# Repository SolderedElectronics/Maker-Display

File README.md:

# Maker Display
## Image

[Crowdsupply campaign][CF]

## Description and details
Maker LED display brings simplicity when it comes to using LED Matrix Displays. Ready to use, assembled circuit board has everything you need to run the display - just plug it in! Arduino library written for it and a dozen pre-made examples make using and customization of the display a trivial task. Not to forget the WiFi connection which enables board to get various info and show it to you. There’s more than just customization of content shown on the display! Choose between 32 x 9 pixels or 64 x 9 pixels version and pick the LED color: white, blue, green, orange or purple.

## Repository content
This repo contains Cadsoft Eagle .sch and .brd files for the board. It also contains schematic in .pdf created from .sch Eagle file. 
Files have been arranged into folders for navigating between different versions of board. 
Tip: layer 200 shows top silkscreen and layer 208 should be bottom silkscreen. tParts and bParts are not used.

## Docs
- [Maker Display Campaign][CF]
- [Maker Display Arduino Library][library]

## Board versions
- v1.0 - inital version

## License info
This product is open-source. Yay!
For any tech questions, contact us at techsupport@e-radionica.com
If you find an Issue, please open one at GitHub. If you can improve our product, fork it!

e-r.io Team.

[library]: #
[CF]: https://www.crowdsupply.com/e-radionica/maker-led-display

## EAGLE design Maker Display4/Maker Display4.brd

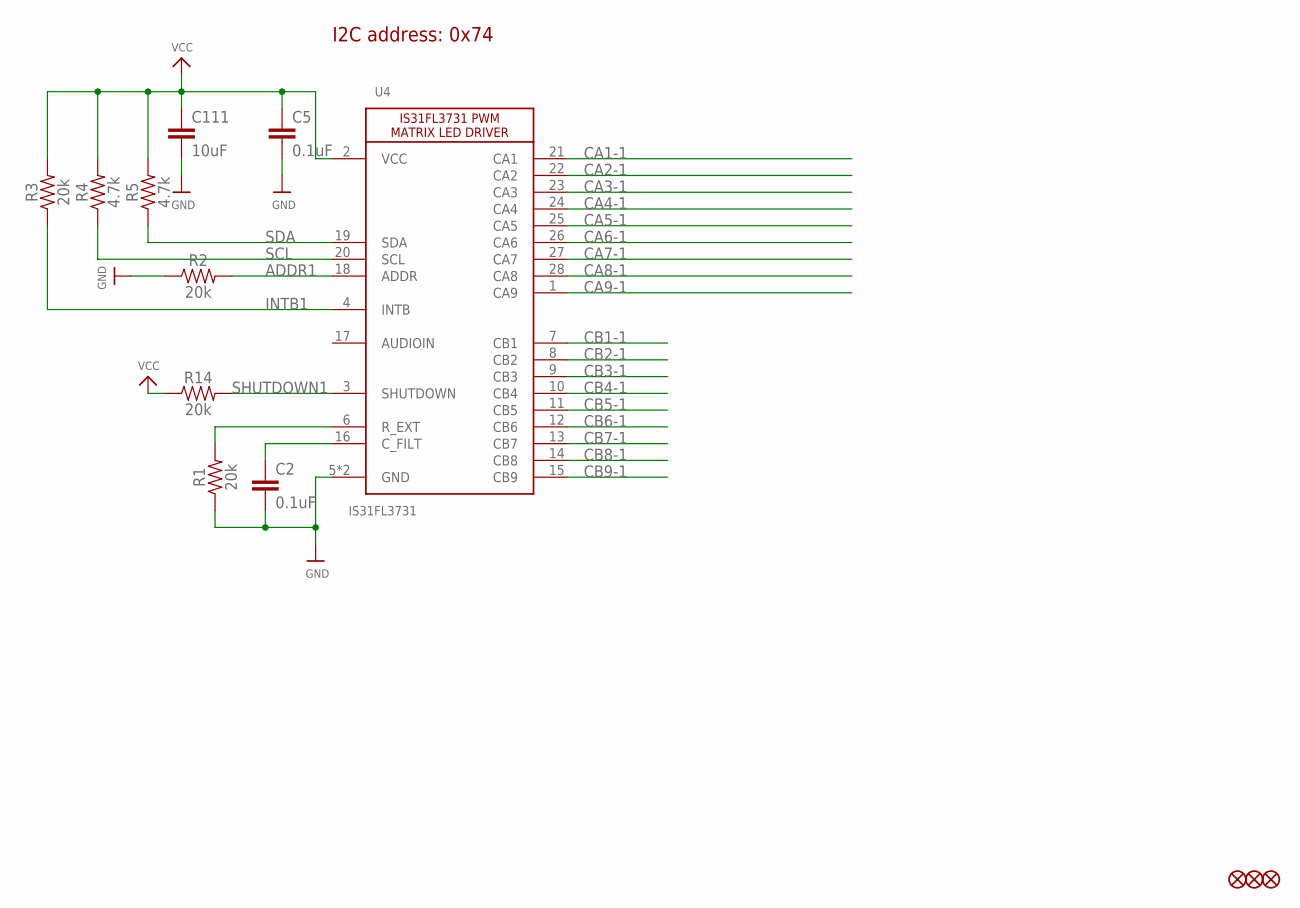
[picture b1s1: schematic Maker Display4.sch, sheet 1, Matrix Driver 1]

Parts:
C2, C5: 0.1uF; 0603
C111: 10uF; 1206
JP2, JP3, JP4: FIDUCIAL1X2; FIDUCIAL-1X2
R1, R2, R3, R14: 20k; 0603
R4, R5: 4.7k; 0603
U4: IS31FL3731; QFN28

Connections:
ADDR1: R2.2, U4.18 (ADDR)
CA1-1: U4.21 (CA1); also elsewhere on the board
CA2-1: U4.22 (CA2); also elsewhere on the board
CA3-1: U4.23 (CA3); also elsewhere on the board
CA4-1: U4.24 (CA4); also elsewhere on the board
CA5-1: U4.25 (CA5); also elsewhere on the board
CA6-1: U4.26 (CA6); also elsewhere on the board
CA7-1: U4.27 (CA7); also elsewhere on the board
CA8-1: U4.28 (CA8); also elsewhere on the board
CA9-1: U4.1 (CA9); also elsewhere on the board
CB1-1: U4.7 (CB1); also elsewhere on the board
CB2-1: U4.8 (CB2); also elsewhere on the board
CB3-1: U4.9 (CB3); also elsewhere on the board
CB4-1: U4.10 (CB4); also elsewhere on the board
CB5-1: U4.11 (CB5); also elsewhere on the board
CB6-1: U4.12 (CB6); also elsewhere on the board
CB7-1: U4.13 (CB7); also elsewhere on the board
CB8-1: U4.14 (CB8); also elsewhere on the board
CB9-1: U4.15 (CB9); also elsewhere on the board
GND: C2.2, C5.2, C111.2, R1.1, R2.1, U4.5 (GND), U4.29_GND (GND); also elsewhere on the board
INTB1: R3.1, U4.4 (INTB)
unnamed: C2.1, U4.16 (C_FILT)
unnamed: R1.2, U4.6 (R_EXT)
SCL: R4.1, U4.20 (SCL); also elsewhere on the board
SDA: R5.1, U4.19 (SDA); also elsewhere on the board
SHUTDOWN1: R14.2, U4.3 (SHUTDOWN)
VCC: C5.1, C111.1, R3.2, R4.2, R5.2, R14.1, U4.2 (VCC); also elsewhere on the board

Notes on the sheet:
I2C address: 0x74

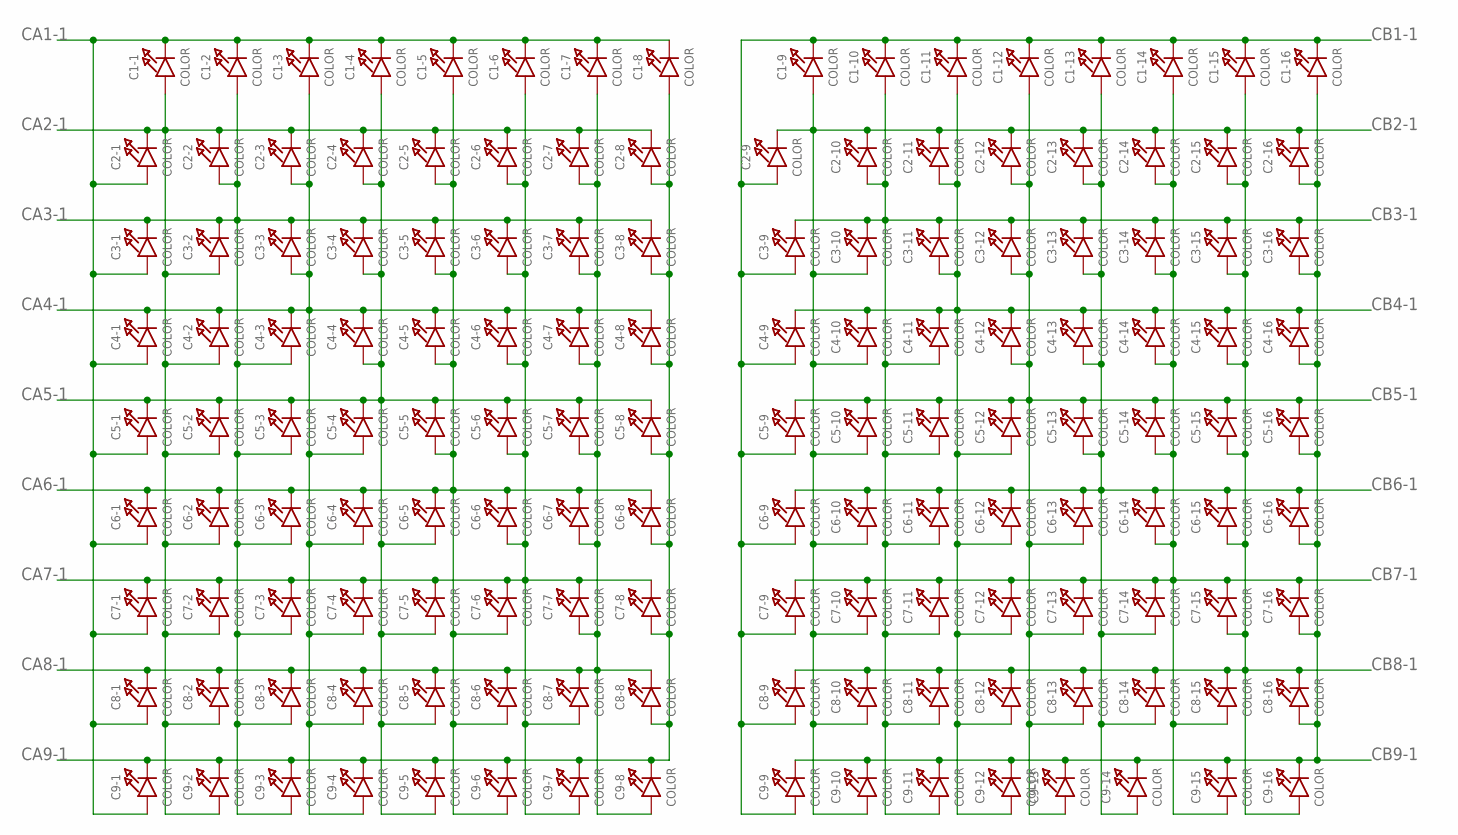
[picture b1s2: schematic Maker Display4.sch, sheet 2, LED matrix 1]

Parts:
C1-1, C1-2, C1-3, C1-4, C1-5, C1-6, C1-7, C1-8, C1-9, C1-10, C1-11, C1-12, C1-13, C1-14, C1-15, C1-16, C2-1, C2-2, C2-3, C2-4, C2-5, C2-6, C2-7, C2-8, C2-9, C2-10, C2-11, C2-12, C2-13, C2-14, C2-15, C2-16, C3-1, C3-2, C3-3, C3-4, C3-5, C3-6, C3-7, C3-8, C3-9, C3-10, C3-11, C3-12, C3-13, C3-14, C3-15, C3-16, C4-1, C4-2, C4-3, C4-4, C4-5, C4-6, C4-7, C4-8, C4-9, C4-10, C4-11, C4-12, C4-13, C4-14, C4-15, C4-16, C5-1, C5-2, C5-3, C5-4, C5-5, C5-6, C5-7, C5-8, C5-9, C5-10, C5-11, C5-12, C5-13, C5-14, C5-15, C5-16, C6-1, C6-2, C6-3, C6-4, C6-5, C6-6, C6-7, C6-8, C6-9, C6-10, C6-11, C6-12, C6-13, C6-14, C6-15, C6-16, C7-1, C7-2, C7-3, C7-4, C7-5, C7-6, C7-7, C7-8, C7-9, C7-10, C7-11, C7-12, C7-13, C7-14, C7-15, C7-16, C8-1, C8-2, C8-3, C8-4, C8-5, C8-6, C8-7, C8-8, C8-9, C8-10, C8-11, C8-12, C8-13, C8-14, C8-15, C8-16, C9-1, C9-2, C9-3, C9-4, C9-5, C9-6, C9-7, C9-8, C9-9, C9-10, C9-11, C9-12, C9-13, C9-14, C9-15, C9-16: COLOR; CHIPLED_0603_NOOUTLINE

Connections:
CA1-1: C1-1.C, C1-2.C, C1-3.C, C1-4.C, C1-5.C, C1-6.C, C1-7.C, C1-8.C, C2-1.A, C3-1.A, C4-1.A, C5-1.A, C6-1.A, C7-1.A, C8-1.A, C9-1.A; also elsewhere on the board
CA2-1: C1-1.A, C2-1.C, C2-2.C, C2-3.C, C2-4.C, C2-5.C, C2-6.C, C2-7.C, C2-8.C, C3-2.A, C4-2.A, C5-2.A, C6-2.A, C7-2.A, C8-2.A, C9-2.A; also elsewhere on the board
CA3-1: C1-2.A, C2-2.A, C3-1.C, C3-2.C, C3-3.C, C3-4.C, C3-5.C, C3-6.C, C3-7.C, C3-8.C, C4-3.A, C5-3.A, C6-3.A, C7-3.A, C8-3.A, C9-3.A; also elsewhere on the board
CA4-1: C1-3.A, C2-3.A, C3-3.A, C4-1.C, C4-2.C, C4-3.C, C4-4.C, C4-5.C, C4-6.C, C4-7.C, C4-8.C, C5-4.A, C6-4.A, C7-4.A, C8-4.A, C9-4.A; also elsewhere on the board
CA5-1: C1-4.A, C2-4.A, C3-4.A, C4-4.A, C5-1.C, C5-2.C, C5-3.C, C5-4.C, C5-5.C, C5-6.C, C5-7.C, C5-8.C, C6-5.A, C7-5.A, C8-5.A, C9-5.A; also elsewhere on the board
CA6-1: C1-5.A, C2-5.A, C3-5.A, C4-5.A, C5-5.A, C6-1.C, C6-2.C, C6-3.C, C6-4.C, C6-5.C, C6-6.C, C6-7.C, C6-8.C, C7-6.A, C8-6.A, C9-6.A; also elsewhere on the board
CA7-1: C1-6.A, C2-6.A, C3-6.A, C4-6.A, C5-6.A, C6-6.A, C7-1.C, C7-2.C, C7-3.C, C7-4.C, C7-5.C, C7-6.C, C7-7.C, C7-8.C, C8-7.A, C9-7.A; also elsewhere on the board
CA8-1: C1-7.A, C2-7.A, C3-7.A, C4-7.A, C5-7.A, C6-7.A, C7-7.A, C8-1.C, C8-2.C, C8-3.C, C8-4.C, C8-5.C, C8-6.C, C8-7.C, C8-8.C, C9-8.A; also elsewhere on the board
CA9-1: C1-8.A, C2-8.A, C3-8.A, C4-8.A, C5-8.A, C6-8.A, C7-8.A, C8-8.A, C9-1.C, C9-2.C, C9-3.C, C9-4.C, C9-5.C, C9-6.C, C9-7.C, C9-8.C; also elsewhere on the board
CB1-1: C1-9.C, C1-10.C, C1-11.C, C1-12.C, C1-13.C, C1-14.C, C1-15.C, C1-16.C, C2-9.A, C3-9.A, C4-9.A, C5-9.A, C6-9.A, C7-9.A, C8-9.A, C9-9.A; also elsewhere on the board
CB2-1: C1-9.A, C2-9.C, C2-10.C, C2-11.C, C2-12.C, C2-13.C, C2-14.C, C2-15.C, C2-16.C, C3-10.A, C4-10.A, C5-10.A, C6-10.A, C7-10.A, C8-10.A, C9-10.A; also elsewhere on the board
CB3-1: C1-10.A, C2-10.A, C3-9.C, C3-10.C, C3-11.C, C3-12.C, C3-13.C, C3-14.C, C3-15.C, C3-16.C, C4-11.A, C5-11.A, C6-11.A, C7-11.A, C8-11.A, C9-11.A; also elsewhere on the board
CB4-1: C1-11.A, C2-11.A, C3-11.A, C4-9.C, C4-10.C, C4-11.C, C4-12.C, C4-13.C, C4-14.C, C4-15.C, C4-16.C, C5-12.A, C6-12.A, C7-12.A, C8-12.A, C9-12.A; also elsewhere on the board
CB5-1: C1-12.A, C2-12.A, C3-12.A, C4-12.A, C5-9.C, C5-10.C, C5-11.C, C5-12.C, C5-13.C, C5-14.C, C5-15.C, C5-16.C, C6-13.A, C7-13.A, C8-13.A, C9-13.A; also elsewhere on the board
CB6-1: C1-13.A, C2-13.A, C3-13.A, C4-13.A, C5-13.A, C6-9.C, C6-10.C, C6-11.C, C6-12.C, C6-13.C, C6-14.C, C6-15.C, C6-16.C, C7-14.A, C8-14.A, C9-14.A; also elsewhere on the board
CB7-1: C1-14.A, C2-14.A, C3-14.A, C4-14.A, C5-14.A, C6-14.A, C7-9.C, C7-10.C, C7-11.C, C7-12.C, C7-13.C, C7-14.C, C7-15.C, C7-16.C, C8-15.A, C9-15.A; also elsewhere on the board
CB8-1: C1-15.A, C2-15.A, C3-15.A, C4-15.A, C5-15.A, C6-15.A, C7-15.A, C8-9.C, C8-10.C, C8-11.C, C8-12.C, C8-13.C, C8-14.C, C8-15.C, C8-16.C, C9-16.A; also elsewhere on the board
CB9-1: C1-16.A, C2-16.A, C3-16.A, C4-16.A, C5-16.A, C6-16.A, C7-16.A, C8-16.A, C9-9.C, C9-10.C, C9-11.C, C9-12.C, C9-13.C, C9-14.C, C9-15.C, C9-16.C; also elsewhere on the board

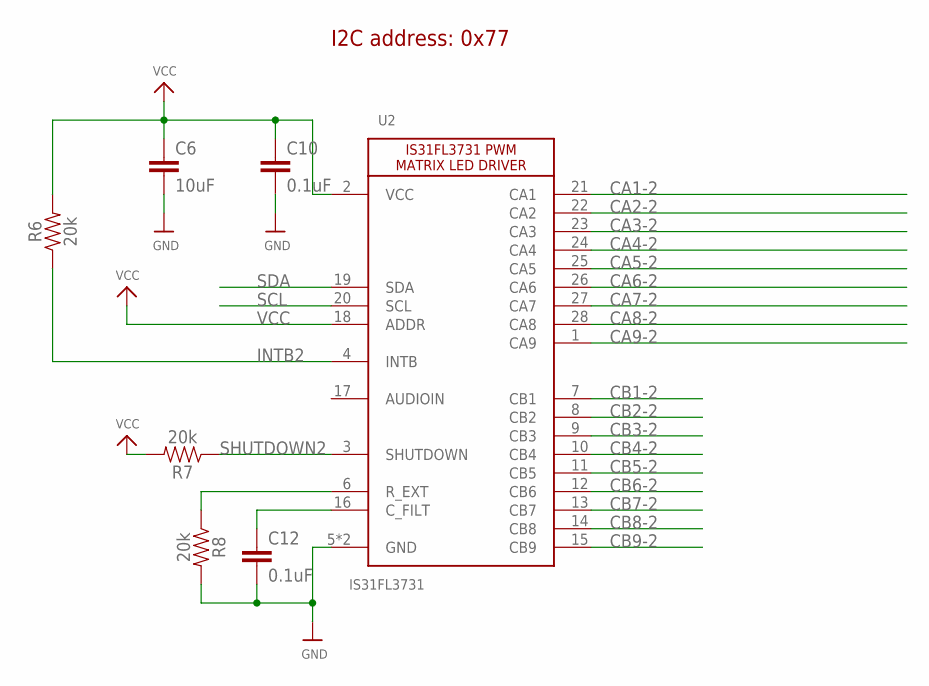
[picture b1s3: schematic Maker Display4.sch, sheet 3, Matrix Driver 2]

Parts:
C6: 10uF; 1206
C10, C12: 0.1uF; 0603
R6, R7, R8: 20k; 0603
U2: IS31FL3731; QFN28

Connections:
CA1-2: U2.21 (CA1); also elsewhere on the board
CA2-2: U2.22 (CA2); also elsewhere on the board
CA3-2: U2.23 (CA3); also elsewhere on the board
CA4-2: U2.24 (CA4); also elsewhere on the board
CA5-2: U2.25 (CA5); also elsewhere on the board
CA6-2: U2.26 (CA6); also elsewhere on the board
CA7-2: U2.27 (CA7); also elsewhere on the board
CA8-2: U2.28 (CA8); also elsewhere on the board
CA9-2: U2.1 (CA9); also elsewhere on the board
CB1-2: U2.7 (CB1); also elsewhere on the board
CB2-2: U2.8 (CB2); also elsewhere on the board
CB3-2: U2.9 (CB3); also elsewhere on the board
CB4-2: U2.10 (CB4); also elsewhere on the board
CB5-2: U2.11 (CB5); also elsewhere on the board
CB6-2: U2.12 (CB6); also elsewhere on the board
CB7-2: U2.13 (CB7); also elsewhere on the board
CB8-2: U2.14 (CB8); also elsewhere on the board
CB9-2: U2.15 (CB9); also elsewhere on the board
GND: C6.2, C10.2, C12.2, R8.2, U2.5 (GND), U2.29_GND (GND); also elsewhere on the board
INTB2: R6.1, U2.4 (INTB)
unnamed: C12.1, U2.16 (C_FILT)
unnamed: R8.1, U2.6 (R_EXT)
SCL: U2.20 (SCL); also elsewhere on the board
SDA: U2.19 (SDA); also elsewhere on the board
SHUTDOWN2: R7.1, U2.3 (SHUTDOWN)
VCC: C6.1, C10.1, R6.2, R7.2, U2.2 (VCC), U2.18 (ADDR); also elsewhere on the board

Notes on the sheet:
I2C address: 0x77

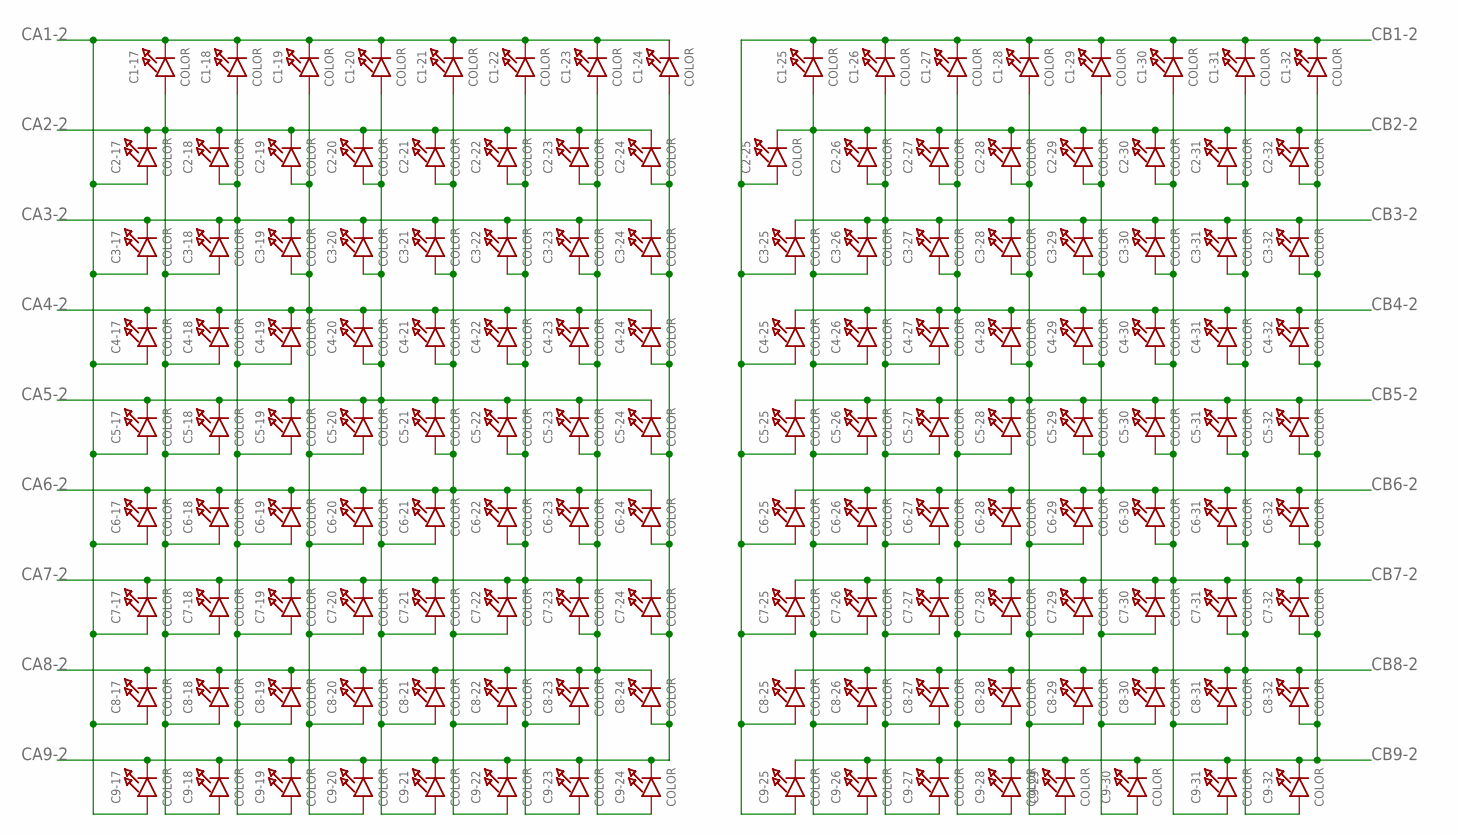
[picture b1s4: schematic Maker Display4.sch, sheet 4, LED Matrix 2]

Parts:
C1-17, C1-18, C1-19, C1-20, C1-21, C1-22, C1-23, C1-24, C1-25, C1-26, C1-27, C1-28, C1-29, C1-30, C1-31, C1-32, C2-17, C2-18, C2-19, C2-20, C2-21, C2-22, C2-23, C2-24, C2-25, C2-26, C2-27, C2-28, C2-29, C2-30, C2-31, C2-32, C3-17, C3-18, C3-19, C3-20, C3-21, C3-22, C3-23, C3-24, C3-25, C3-26, C3-27, C3-28, C3-29, C3-30, C3-31, C3-32, C4-17, C4-18, C4-19, C4-20, C4-21, C4-22, C4-23, C4-24, C4-25, C4-26, C4-27, C4-28, C4-29, C4-30, C4-31, C4-32, C5-17, C5-18, C5-19, C5-20, C5-21, C5-22, C5-23, C5-24, C5-25, C5-26, C5-27, C5-28, C5-29, C5-30, C5-31, C5-32, C6-17, C6-18, C6-19, C6-20, C6-21, C6-22, C6-23, C6-24, C6-25, C6-26, C6-27, C6-28, C6-29, C6-30, C6-31, C6-32, C7-17, C7-18, C7-19, C7-20, C7-21, C7-22, C7-23, C7-24, C7-25, C7-26, C7-27, C7-28, C7-29, C7-30, C7-31, C7-32, C8-17, C8-18, C8-19, C8-20, C8-21, C8-22, C8-23, C8-24, C8-25, C8-26, C8-27, C8-28, C8-29, C8-30, C8-31, C8-32, C9-17, C9-18, C9-19, C9-20, C9-21, C9-22, C9-23, C9-24, C9-25, C9-26, C9-27, C9-28, C9-29, C9-30, C9-31, C9-32: COLOR; CHIPLED_0603_NOOUTLINE

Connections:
CA1-2: C1-17.C, C1-18.C, C1-19.C, C1-20.C, C1-21.C, C1-22.C, C1-23.C, C1-24.C, C2-17.A, C3-17.A, C4-17.A, C5-17.A, C6-17.A, C7-17.A, C8-17.A, C9-17.A; also elsewhere on the board
CA2-2: C1-17.A, C2-17.C, C2-18.C, C2-19.C, C2-20.C, C2-21.C, C2-22.C, C2-23.C, C2-24.C, C3-18.A, C4-18.A, C5-18.A, C6-18.A, C7-18.A, C8-18.A, C9-18.A; also elsewhere on the board
CA3-2: C1-18.A, C2-18.A, C3-17.C, C3-18.C, C3-19.C, C3-20.C, C3-21.C, C3-22.C, C3-23.C, C3-24.C, C4-19.A, C5-19.A, C6-19.A, C7-19.A, C8-19.A, C9-19.A; also elsewhere on the board
CA4-2: C1-19.A, C2-19.A, C3-19.A, C4-17.C, C4-18.C, C4-19.C, C4-20.C, C4-21.C, C4-22.C, C4-23.C, C4-24.C, C5-20.A, C6-20.A, C7-20.A, C8-20.A, C9-20.A; also elsewhere on the board
CA5-2: C1-20.A, C2-20.A, C3-20.A, C4-20.A, C5-17.C, C5-18.C, C5-19.C, C5-20.C, C5-21.C, C5-22.C, C5-23.C, C5-24.C, C6-21.A, C7-21.A, C8-21.A, C9-21.A; also elsewhere on the board
CA6-2: C1-21.A, C2-21.A, C3-21.A, C4-21.A, C5-21.A, C6-17.C, C6-18.C, C6-19.C, C6-20.C, C6-21.C, C6-22.C, C6-23.C, C6-24.C, C7-22.A, C8-22.A, C9-22.A; also elsewhere on the board
CA7-2: C1-22.A, C2-22.A, C3-22.A, C4-22.A, C5-22.A, C6-22.A, C7-17.C, C7-18.C, C7-19.C, C7-20.C, C7-21.C, C7-22.C, C7-23.C, C7-24.C, C8-23.A, C9-23.A; also elsewhere on the board
CA8-2: C1-23.A, C2-23.A, C3-23.A, C4-23.A, C5-23.A, C6-23.A, C7-23.A, C8-17.C, C8-18.C, C8-19.C, C8-20.C, C8-21.C, C8-22.C, C8-23.C, C8-24.C, C9-24.A; also elsewhere on the board
CA9-2: C1-24.A, C2-24.A, C3-24.A, C4-24.A, C5-24.A, C6-24.A, C7-24.A, C8-24.A, C9-17.C, C9-18.C, C9-19.C, C9-20.C, C9-21.C, C9-22.C, C9-23.C, C9-24.C; also elsewhere on the board
CB1-2: C1-25.C, C1-26.C, C1-27.C, C1-28.C, C1-29.C, C1-30.C, C1-31.C, C1-32.C, C2-25.A, C3-25.A, C4-25.A, C5-25.A, C6-25.A, C7-25.A, C8-25.A, C9-25.A; also elsewhere on the board
CB2-2: C1-25.A, C2-25.C, C2-26.C, C2-27.C, C2-28.C, C2-29.C, C2-30.C, C2-31.C, C2-32.C, C3-26.A, C4-26.A, C5-26.A, C6-26.A, C7-26.A, C8-26.A, C9-26.A; also elsewhere on the board
CB3-2: C1-26.A, C2-26.A, C3-25.C, C3-26.C, C3-27.C, C3-28.C, C3-29.C, C3-30.C, C3-31.C, C3-32.C, C4-27.A, C5-27.A, C6-27.A, C7-27.A, C8-27.A, C9-27.A; also elsewhere on the board
CB4-2: C1-27.A, C2-27.A, C3-27.A, C4-25.C, C4-26.C, C4-27.C, C4-28.C, C4-29.C, C4-30.C, C4-31.C, C4-32.C, C5-28.A, C6-28.A, C7-28.A, C8-28.A, C9-28.A; also elsewhere on the board
CB5-2: C1-28.A, C2-28.A, C3-28.A, C4-28.A, C5-25.C, C5-26.C, C5-27.C, C5-28.C, C5-29.C, C5-30.C, C5-31.C, C5-32.C, C6-29.A, C7-29.A, C8-29.A, C9-29.A; also elsewhere on the board
CB6-2: C1-29.A, C2-29.A, C3-29.A, C4-29.A, C5-29.A, C6-25.C, C6-26.C, C6-27.C, C6-28.C, C6-29.C, C6-30.C, C6-31.C, C6-32.C, C7-30.A, C8-30.A, C9-30.A; also elsewhere on the board
CB7-2: C1-30.A, C2-30.A, C3-30.A, C4-30.A, C5-30.A, C6-30.A, C7-25.C, C7-26.C, C7-27.C, C7-28.C, C7-29.C, C7-30.C, C7-31.C, C7-32.C, C8-31.A, C9-31.A; also elsewhere on the board
CB8-2: C1-31.A, C2-31.A, C3-31.A, C4-31.A, C5-31.A, C6-31.A, C7-31.A, C8-25.C, C8-26.C, C8-27.C, C8-28.C, C8-29.C, C8-30.C, C8-31.C, C8-32.C, C9-32.A; also elsewhere on the board
CB9-2: C1-32.A, C2-32.A, C3-32.A, C4-32.A, C5-32.A, C6-32.A, C7-32.A, C8-32.A, C9-25.C, C9-26.C, C9-27.C, C9-28.C, C9-29.C, C9-30.C, C9-31.C, C9-32.C; also elsewhere on the board

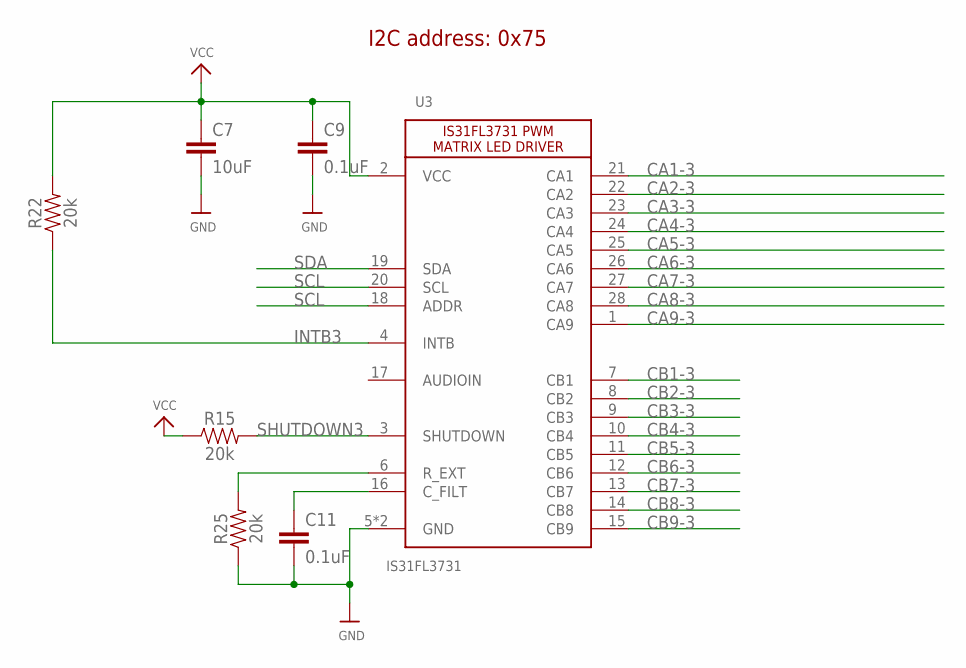
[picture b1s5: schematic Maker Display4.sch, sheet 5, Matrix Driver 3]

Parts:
C7: 10uF; 1206
C9, C11: 0.1uF; 0603
R15, R22, R25: 20k; 0603
U3: IS31FL3731; QFN28

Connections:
CA1-3: U3.21 (CA1); also elsewhere on the board
CA2-3: U3.22 (CA2); also elsewhere on the board
CA3-3: U3.23 (CA3); also elsewhere on the board
CA4-3: U3.24 (CA4); also elsewhere on the board
CA5-3: U3.25 (CA5); also elsewhere on the board
CA6-3: U3.26 (CA6); also elsewhere on the board
CA7-3: U3.27 (CA7); also elsewhere on the board
CA8-3: U3.28 (CA8); also elsewhere on the board
CA9-3: U3.1 (CA9); also elsewhere on the board
CB1-3: U3.7 (CB1); also elsewhere on the board
CB2-3: U3.8 (CB2); also elsewhere on the board
CB3-3: U3.9 (CB3); also elsewhere on the board
CB4-3: U3.10 (CB4); also elsewhere on the board
CB5-3: U3.11 (CB5); also elsewhere on the board
CB6-3: U3.12 (CB6); also elsewhere on the board
CB7-3: U3.13 (CB7); also elsewhere on the board
CB8-3: U3.14 (CB8); also elsewhere on the board
CB9-3: U3.15 (CB9); also elsewhere on the board
GND: C7.2, C9.2, C11.2, R25.1, U3.5 (GND), U3.29_GND (GND); also elsewhere on the board
INTB3: R22.1, U3.4 (INTB)
unnamed: C11.1, U3.16 (C_FILT)
unnamed: R25.2, U3.6 (R_EXT)
SCL: U3.18 (ADDR), U3.20 (SCL); also elsewhere on the board
SDA: U3.19 (SDA); also elsewhere on the board
SHUTDOWN3: R15.2, U3.3 (SHUTDOWN)
VCC: C7.1, C9.1, R15.1, R22.2, U3.2 (VCC); also elsewhere on the board

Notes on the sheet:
I2C address: 0x75

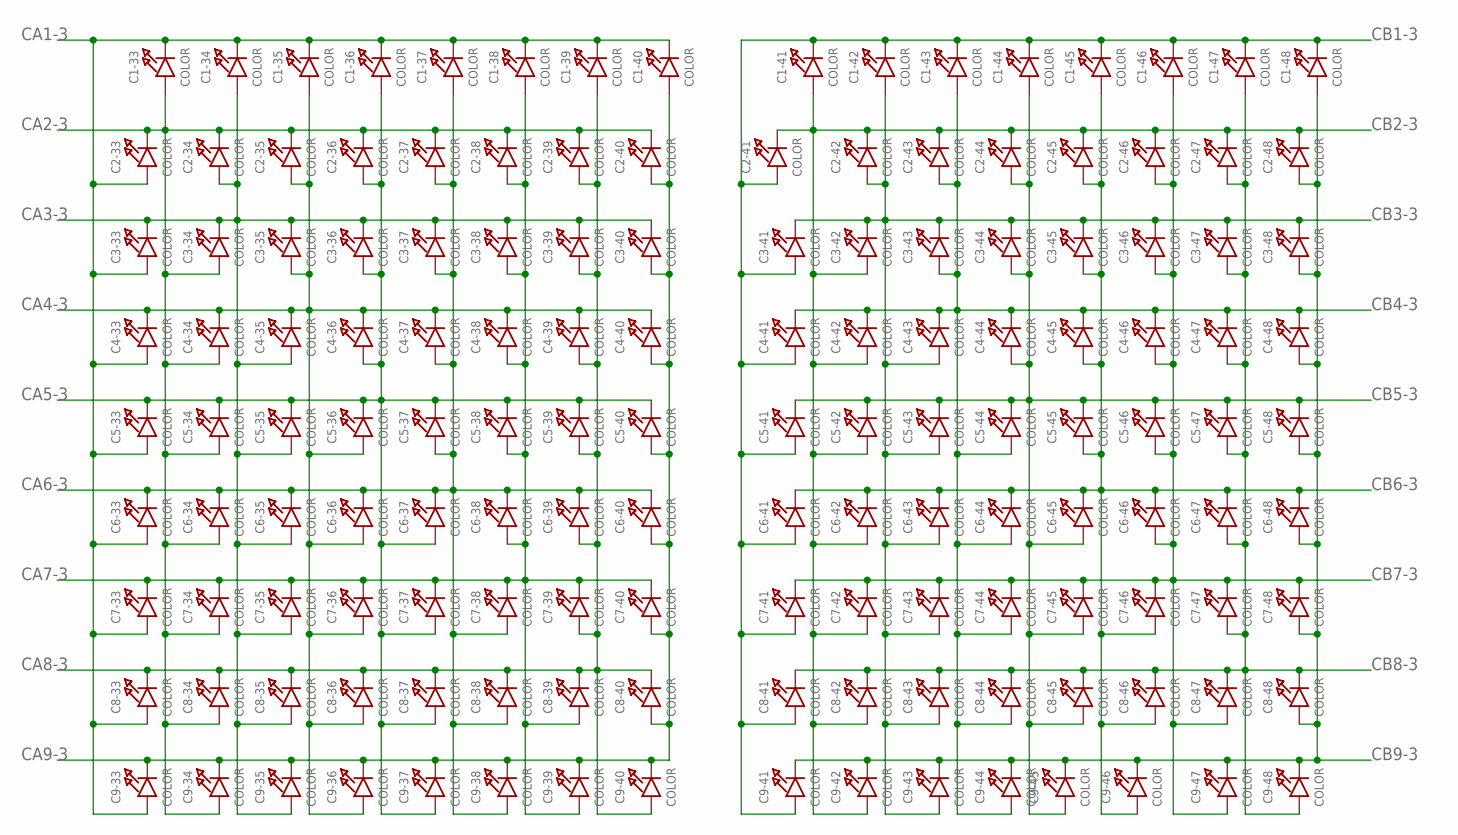
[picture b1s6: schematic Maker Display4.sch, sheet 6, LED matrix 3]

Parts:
C1-33, C1-34, C1-35, C1-36, C1-37, C1-38, C1-39, C1-40, C1-41, C1-42, C1-43, C1-44, C1-45, C1-46, C1-47, C1-48, C2-33, C2-34, C2-35, C2-36, C2-37, C2-38, C2-39, C2-40, C2-41, C2-42, C2-43, C2-44, C2-45, C2-46, C2-47, C2-48, C3-33, C3-34, C3-35, C3-36, C3-37, C3-38, C3-39, C3-40, C3-41, C3-42, C3-43, C3-44, C3-45, C3-46, C3-47, C3-48, C4-33, C4-34, C4-35, C4-36, C4-37, C4-38, C4-39, C4-40, C4-41, C4-42, C4-43, C4-44, C4-45, C4-46, C4-47, C4-48, C5-33, C5-34, C5-35, C5-36, C5-37, C5-38, C5-39, C5-40, C5-41, C5-42, C5-43, C5-44, C5-45, C5-46, C5-47, C5-48, C6-33, C6-34, C6-35, C6-36, C6-37, C6-38, C6-39, C6-40, C6-41, C6-42, C6-43, C6-44, C6-45, C6-46, C6-47, C6-48, C7-33, C7-34, C7-35, C7-36, C7-37, C7-38, C7-39, C7-40, C7-41, C7-42, C7-43, C7-44, C7-45, C7-46, C7-47, C7-48, C8-33, C8-34, C8-35, C8-36, C8-37, C8-38, C8-39, C8-40, C8-41, C8-42, C8-43, C8-44, C8-45, C8-46, C8-47, C8-48, C9-33, C9-34, C9-35, C9-36, C9-37, C9-38, C9-39, C9-40, C9-41, C9-42, C9-43, C9-44, C9-45, C9-46, C9-47, C9-48: COLOR; CHIPLED_0603_NOOUTLINE

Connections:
CA1-3: C1-33.C, C1-34.C, C1-35.C, C1-36.C, C1-37.C, C1-38.C, C1-39.C, C1-40.C, C2-33.A, C3-33.A, C4-33.A, C5-33.A, C6-33.A, C7-33.A, C8-33.A, C9-33.A; also elsewhere on the board
CA2-3: C1-33.A, C2-33.C, C2-34.C, C2-35.C, C2-36.C, C2-37.C, C2-38.C, C2-39.C, C2-40.C, C3-34.A, C4-34.A, C5-34.A, C6-34.A, C7-34.A, C8-34.A, C9-34.A; also elsewhere on the board
CA3-3: C1-34.A, C2-34.A, C3-33.C, C3-34.C, C3-35.C, C3-36.C, C3-37.C, C3-38.C, C3-39.C, C3-40.C, C4-35.A, C5-35.A, C6-35.A, C7-35.A, C8-35.A, C9-35.A; also elsewhere on the board
CA4-3: C1-35.A, C2-35.A, C3-35.A, C4-33.C, C4-34.C, C4-35.C, C4-36.C, C4-37.C, C4-38.C, C4-39.C, C4-40.C, C5-36.A, C6-36.A, C7-36.A, C8-36.A, C9-36.A; also elsewhere on the board
CA5-3: C1-36.A, C2-36.A, C3-36.A, C4-36.A, C5-33.C, C5-34.C, C5-35.C, C5-36.C, C5-37.C, C5-38.C, C5-39.C, C5-40.C, C6-37.A, C7-37.A, C8-37.A, C9-37.A; also elsewhere on the board
CA6-3: C1-37.A, C2-37.A, C3-37.A, C4-37.A, C5-37.A, C6-33.C, C6-34.C, C6-35.C, C6-36.C, C6-37.C, C6-38.C, C6-39.C, C6-40.C, C7-38.A, C8-38.A, C9-38.A; also elsewhere on the board
CA7-3: C1-38.A, C2-38.A, C3-38.A, C4-38.A, C5-38.A, C6-38.A, C7-33.C, C7-34.C, C7-35.C, C7-36.C, C7-37.C, C7-38.C, C7-39.C, C7-40.C, C8-39.A, C9-39.A; also elsewhere on the board
CA8-3: C1-39.A, C2-39.A, C3-39.A, C4-39.A, C5-39.A, C6-39.A, C7-39.A, C8-33.C, C8-34.C, C8-35.C, C8-36.C, C8-37.C, C8-38.C, C8-39.C, C8-40.C, C9-40.A; also elsewhere on the board
CA9-3: C1-40.A, C2-40.A, C3-40.A, C4-40.A, C5-40.A, C6-40.A, C7-40.A, C8-40.A, C9-33.C, C9-34.C, C9-35.C, C9-36.C, C9-37.C, C9-38.C, C9-39.C, C9-40.C; also elsewhere on the board
CB1-3: C1-41.C, C1-42.C, C1-43.C, C1-44.C, C1-45.C, C1-46.C, C1-47.C, C1-48.C, C2-41.A, C3-41.A, C4-41.A, C5-41.A, C6-41.A, C7-41.A, C8-41.A, C9-41.A; also elsewhere on the board
CB2-3: C1-41.A, C2-41.C, C2-42.C, C2-43.C, C2-44.C, C2-45.C, C2-46.C, C2-47.C, C2-48.C, C3-42.A, C4-42.A, C5-42.A, C6-42.A, C7-42.A, C8-42.A, C9-42.A; also elsewhere on the board
CB3-3: C1-42.A, C2-42.A, C3-41.C, C3-42.C, C3-43.C, C3-44.C, C3-45.C, C3-46.C, C3-47.C, C3-48.C, C4-43.A, C5-43.A, C6-43.A, C7-43.A, C8-43.A, C9-43.A; also elsewhere on the board
CB4-3: C1-43.A, C2-43.A, C3-43.A, C4-41.C, C4-42.C, C4-43.C, C4-44.C, C4-45.C, C4-46.C, C4-47.C, C4-48.C, C5-44.A, C6-44.A, C7-44.A, C8-44.A, C9-44.A; also elsewhere on the board
CB5-3: C1-44.A, C2-44.A, C3-44.A, C4-44.A, C5-41.C, C5-42.C, C5-43.C, C5-44.C, C5-45.C, C5-46.C, C5-47.C, C5-48.C, C6-45.A, C7-45.A, C8-45.A, C9-45.A; also elsewhere on the board
CB6-3: C1-45.A, C2-45.A, C3-45.A, C4-45.A, C5-45.A, C6-41.C, C6-42.C, C6-43.C, C6-44.C, C6-45.C, C6-46.C, C6-47.C, C6-48.C, C7-46.A, C8-46.A, C9-46.A; also elsewhere on the board
CB7-3: C1-46.A, C2-46.A, C3-46.A, C4-46.A, C5-46.A, C6-46.A, C7-41.C, C7-42.C, C7-43.C, C7-44.C, C7-45.C, C7-46.C, C7-47.C, C7-48.C, C8-47.A, C9-47.A; also elsewhere on the board
CB8-3: C1-47.A, C2-47.A, C3-47.A, C4-47.A, C5-47.A, C6-47.A, C7-47.A, C8-41.C, C8-42.C, C8-43.C, C8-44.C, C8-45.C, C8-46.C, C8-47.C, C8-48.C, C9-48.A; also elsewhere on the board
CB9-3: C1-48.A, C2-48.A, C3-48.A, C4-48.A, C5-48.A, C6-48.A, C7-48.A, C8-48.A, C9-41.C, C9-42.C, C9-43.C, C9-44.C, C9-45.C, C9-46.C, C9-47.C, C9-48.C; also elsewhere on the board

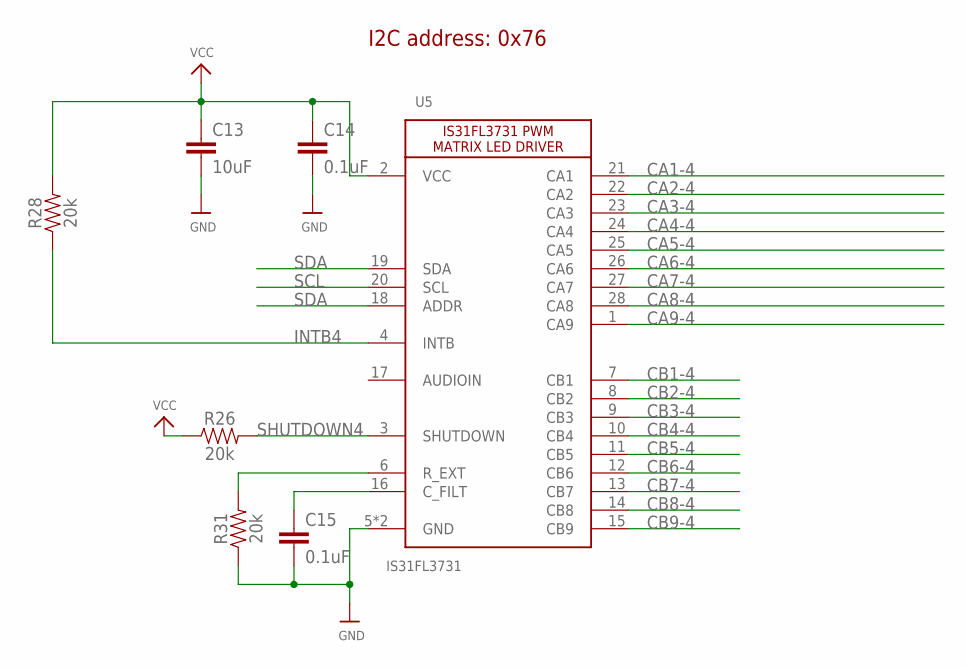
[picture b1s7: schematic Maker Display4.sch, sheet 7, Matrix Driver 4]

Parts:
C13: 10uF; 1206
C14, C15: 0.1uF; 0603
R26, R28, R31: 20k; 0603
U5: IS31FL3731; QFN28

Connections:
CA1-4: U5.21 (CA1); also elsewhere on the board
CA2-4: U5.22 (CA2); also elsewhere on the board
CA3-4: U5.23 (CA3); also elsewhere on the board
CA4-4: U5.24 (CA4); also elsewhere on the board
CA5-4: U5.25 (CA5); also elsewhere on the board
CA6-4: U5.26 (CA6); also elsewhere on the board
CA7-4: U5.27 (CA7); also elsewhere on the board
CA8-4: U5.28 (CA8); also elsewhere on the board
CA9-4: U5.1 (CA9); also elsewhere on the board
CB1-4: U5.7 (CB1); also elsewhere on the board
CB2-4: U5.8 (CB2); also elsewhere on the board
CB3-4: U5.9 (CB3); also elsewhere on the board
CB4-4: U5.10 (CB4); also elsewhere on the board
CB5-4: U5.11 (CB5); also elsewhere on the board
CB6-4: U5.12 (CB6); also elsewhere on the board
CB7-4: U5.13 (CB7); also elsewhere on the board
CB8-4: U5.14 (CB8); also elsewhere on the board
CB9-4: U5.15 (CB9); also elsewhere on the board
GND: C13.2, C14.2, C15.2, R31.1, U5.5 (GND), U5.29_GND (GND); also elsewhere on the board
INTB4: R28.1, U5.4 (INTB)
unnamed: C15.1, U5.16 (C_FILT)
unnamed: R31.2, U5.6 (R_EXT)
SCL: U5.20 (SCL); also elsewhere on the board
SDA: U5.18 (ADDR), U5.19 (SDA); also elsewhere on the board
SHUTDOWN4: R26.2, U5.3 (SHUTDOWN)
VCC: C13.1, C14.1, R26.1, R28.2, U5.2 (VCC); also elsewhere on the board

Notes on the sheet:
I2C address: 0x76

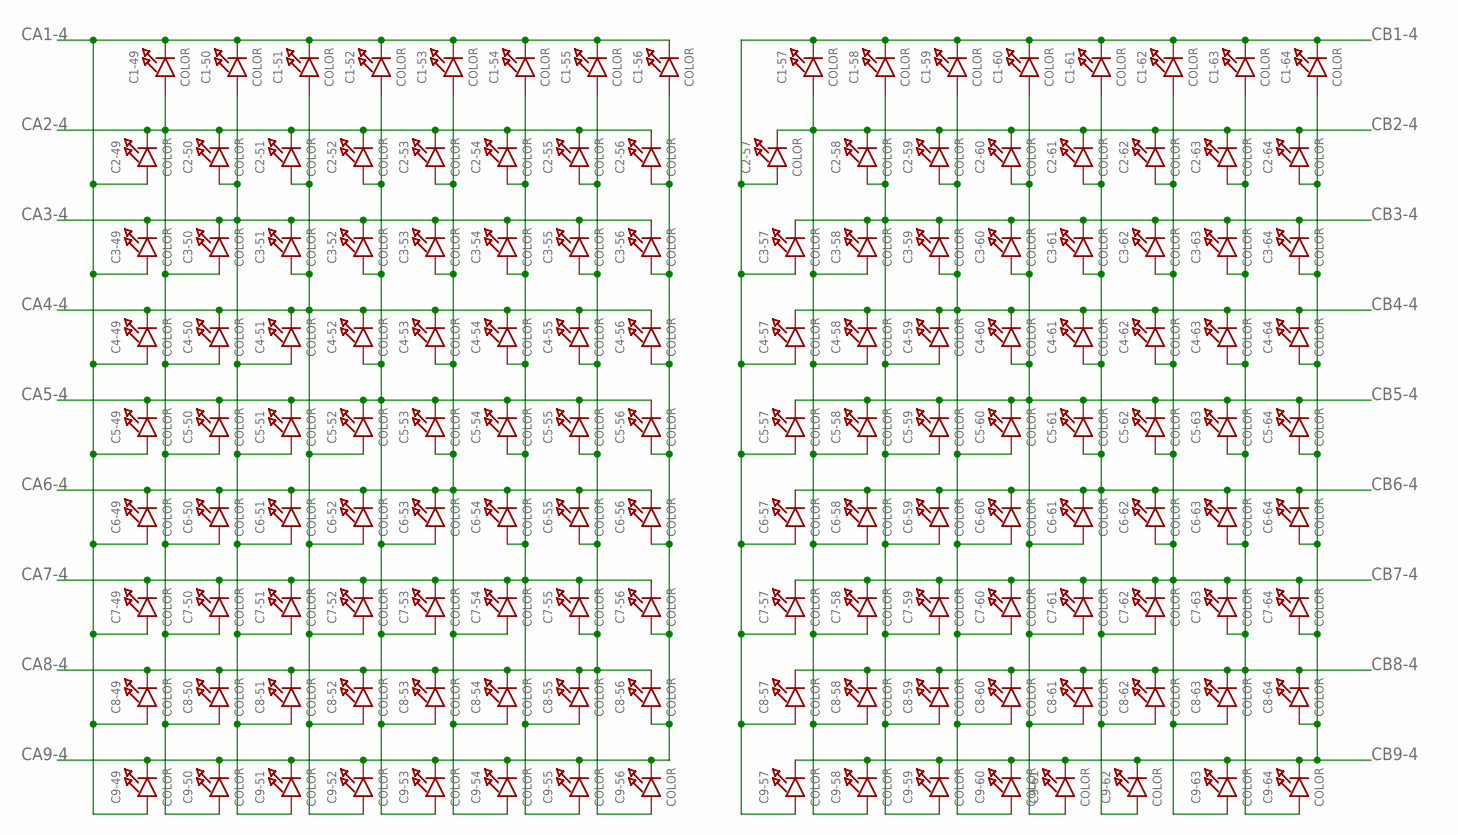
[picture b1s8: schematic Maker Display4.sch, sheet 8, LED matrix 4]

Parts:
C1-49, C1-50, C1-51, C1-52, C1-53, C1-54, C1-55, C1-56, C1-57, C1-58, C1-59, C1-60, C1-61, C1-62, C1-63, C1-64, C2-49, C2-50, C2-51, C2-52, C2-53, C2-54, C2-55, C2-56, C2-57, C2-58, C2-59, C2-60, C2-61, C2-62, C2-63, C2-64, C3-49, C3-50, C3-51, C3-52, C3-53, C3-54, C3-55, C3-56, C3-57, C3-58, C3-59, C3-60, C3-61, C3-62, C3-63, C3-64, C4-49, C4-50, C4-51, C4-52, C4-53, C4-54, C4-55, C4-56, C4-57, C4-58, C4-59, C4-60, C4-61, C4-62, C4-63, C4-64, C5-49, C5-50, C5-51, C5-52, C5-53, C5-54, C5-55, C5-56, C5-57, C5-58, C5-59, C5-60, C5-61, C5-62, C5-63, C5-64, C6-49, C6-50, C6-51, C6-52, C6-53, C6-54, C6-55, C6-56, C6-57, C6-58, C6-59, C6-60, C6-61, C6-62, C6-63, C6-64, C7-49, C7-50, C7-51, C7-52, C7-53, C7-54, C7-55, C7-56, C7-57, C7-58, C7-59, C7-60, C7-61, C7-62, C7-63, C7-64, C8-49, C8-50, C8-51, C8-52, C8-53, C8-54, C8-55, C8-56, C8-57, C8-58, C8-59, C8-60, C8-61, C8-62, C8-63, C8-64, C9-49, C9-50, C9-51, C9-52, C9-53, C9-54, C9-55, C9-56, C9-57, C9-58, C9-59, C9-60, C9-61, C9-62, C9-63, C9-64: COLOR; CHIPLED_0603_NOOUTLINE

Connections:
CA1-4: C1-49.C, C1-50.C, C1-51.C, C1-52.C, C1-53.C, C1-54.C, C1-55.C, C1-56.C, C2-49.A, C3-49.A, C4-49.A, C5-49.A, C6-49.A, C7-49.A, C8-49.A, C9-49.A; also elsewhere on the board
CA2-4: C1-49.A, C2-49.C, C2-50.C, C2-51.C, C2-52.C, C2-53.C, C2-54.C, C2-55.C, C2-56.C, C3-50.A, C4-50.A, C5-50.A, C6-50.A, C7-50.A, C8-50.A, C9-50.A; also elsewhere on the board
CA3-4: C1-50.A, C2-50.A, C3-49.C, C3-50.C, C3-51.C, C3-52.C, C3-53.C, C3-54.C, C3-55.C, C3-56.C, C4-51.A, C5-51.A, C6-51.A, C7-51.A, C8-51.A, C9-51.A; also elsewhere on the board
CA4-4: C1-51.A, C2-51.A, C3-51.A, C4-49.C, C4-50.C, C4-51.C, C4-52.C, C4-53.C, C4-54.C, C4-55.C, C4-56.C, C5-52.A, C6-52.A, C7-52.A, C8-52.A, C9-52.A; also elsewhere on the board
CA5-4: C1-52.A, C2-52.A, C3-52.A, C4-52.A, C5-49.C, C5-50.C, C5-51.C, C5-52.C, C5-53.C, C5-54.C, C5-55.C, C5-56.C, C6-53.A, C7-53.A, C8-53.A, C9-53.A; also elsewhere on the board
CA6-4: C1-53.A, C2-53.A, C3-53.A, C4-53.A, C5-53.A, C6-49.C, C6-50.C, C6-51.C, C6-52.C, C6-53.C, C6-54.C, C6-55.C, C6-56.C, C7-54.A, C8-54.A, C9-54.A; also elsewhere on the board
CA7-4: C1-54.A, C2-54.A, C3-54.A, C4-54.A, C5-54.A, C6-54.A, C7-49.C, C7-50.C, C7-51.C, C7-52.C, C7-53.C, C7-54.C, C7-55.C, C7-56.C, C8-55.A, C9-55.A; also elsewhere on the board
CA8-4: C1-55.A, C2-55.A, C3-55.A, C4-55.A, C5-55.A, C6-55.A, C7-55.A, C8-49.C, C8-50.C, C8-51.C, C8-52.C, C8-53.C, C8-54.C, C8-55.C, C8-56.C, C9-56.A; also elsewhere on the board
CA9-4: C1-56.A, C2-56.A, C3-56.A, C4-56.A, C5-56.A, C6-56.A, C7-56.A, C8-56.A, C9-49.C, C9-50.C, C9-51.C, C9-52.C, C9-53.C, C9-54.C, C9-55.C, C9-56.C; also elsewhere on the board
CB1-4: C1-57.C, C1-58.C, C1-59.C, C1-60.C, C1-61.C, C1-62.C, C1-63.C, C1-64.C, C2-57.A, C3-57.A, C4-57.A, C5-57.A, C6-57.A, C7-57.A, C8-57.A, C9-57.A; also elsewhere on the board
CB2-4: C1-57.A, C2-57.C, C2-58.C, C2-59.C, C2-60.C, C2-61.C, C2-62.C, C2-63.C, C2-64.C, C3-58.A, C4-58.A, C5-58.A, C6-58.A, C7-58.A, C8-58.A, C9-58.A; also elsewhere on the board
CB3-4: C1-58.A, C2-58.A, C3-57.C, C3-58.C, C3-59.C, C3-60.C, C3-61.C, C3-62.C, C3-63.C, C3-64.C, C4-59.A, C5-59.A, C6-59.A, C7-59.A, C8-59.A, C9-59.A; also elsewhere on the board
CB4-4: C1-59.A, C2-59.A, C3-59.A, C4-57.C, C4-58.C, C4-59.C, C4-60.C, C4-61.C, C4-62.C, C4-63.C, C4-64.C, C5-60.A, C6-60.A, C7-60.A, C8-60.A, C9-60.A; also elsewhere on the board
CB5-4: C1-60.A, C2-60.A, C3-60.A, C4-60.A, C5-57.C, C5-58.C, C5-59.C, C5-60.C, C5-61.C, C5-62.C, C5-63.C, C5-64.C, C6-61.A, C7-61.A, C8-61.A, C9-61.A; also elsewhere on the board
CB6-4: C1-61.A, C2-61.A, C3-61.A, C4-61.A, C5-61.A, C6-57.C, C6-58.C, C6-59.C, C6-60.C, C6-61.C, C6-62.C, C6-63.C, C6-64.C, C7-62.A, C8-62.A, C9-62.A; also elsewhere on the board
CB7-4: C1-62.A, C2-62.A, C3-62.A, C4-62.A, C5-62.A, C6-62.A, C7-57.C, C7-58.C, C7-59.C, C7-60.C, C7-61.C, C7-62.C, C7-63.C, C7-64.C, C8-63.A, C9-63.A; also elsewhere on the board
CB8-4: C1-63.A, C2-63.A, C3-63.A, C4-63.A, C5-63.A, C6-63.A, C7-63.A, C8-57.C, C8-58.C, C8-59.C, C8-60.C, C8-61.C, C8-62.C, C8-63.C, C8-64.C, C9-64.A; also elsewhere on the board
CB9-4: C1-64.A, C2-64.A, C3-64.A, C4-64.A, C5-64.A, C6-64.A, C7-64.A, C8-64.A, C9-57.C, C9-58.C, C9-59.C, C9-60.C, C9-61.C, C9-62.C, C9-63.C, C9-64.C; also elsewhere on the board

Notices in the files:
parts and their libraries:
microbuilder: This work is placed in the public domain, and may be freely used for commercial and non-commercial work with the following conditions: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
SparkFun: Licensing: CC v3.0 Share-Alike You are welcome to use this library for commercial purposes.
